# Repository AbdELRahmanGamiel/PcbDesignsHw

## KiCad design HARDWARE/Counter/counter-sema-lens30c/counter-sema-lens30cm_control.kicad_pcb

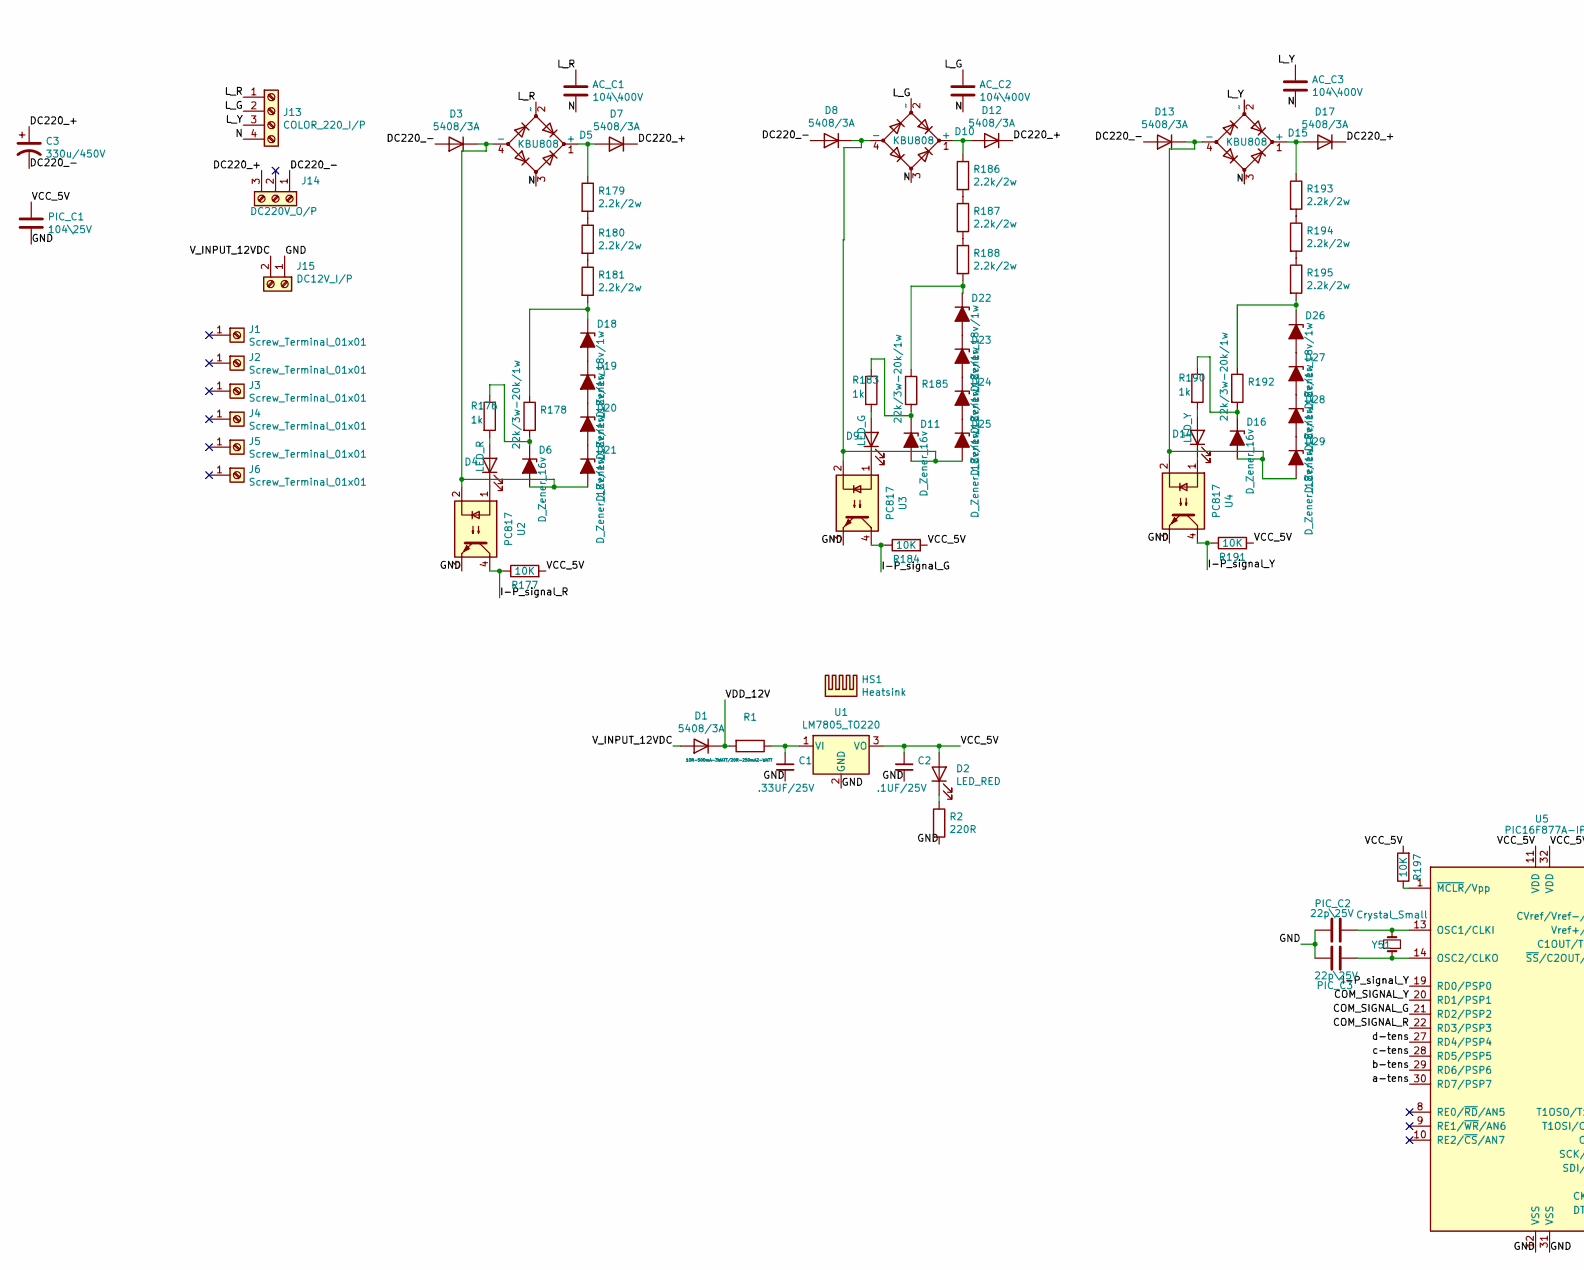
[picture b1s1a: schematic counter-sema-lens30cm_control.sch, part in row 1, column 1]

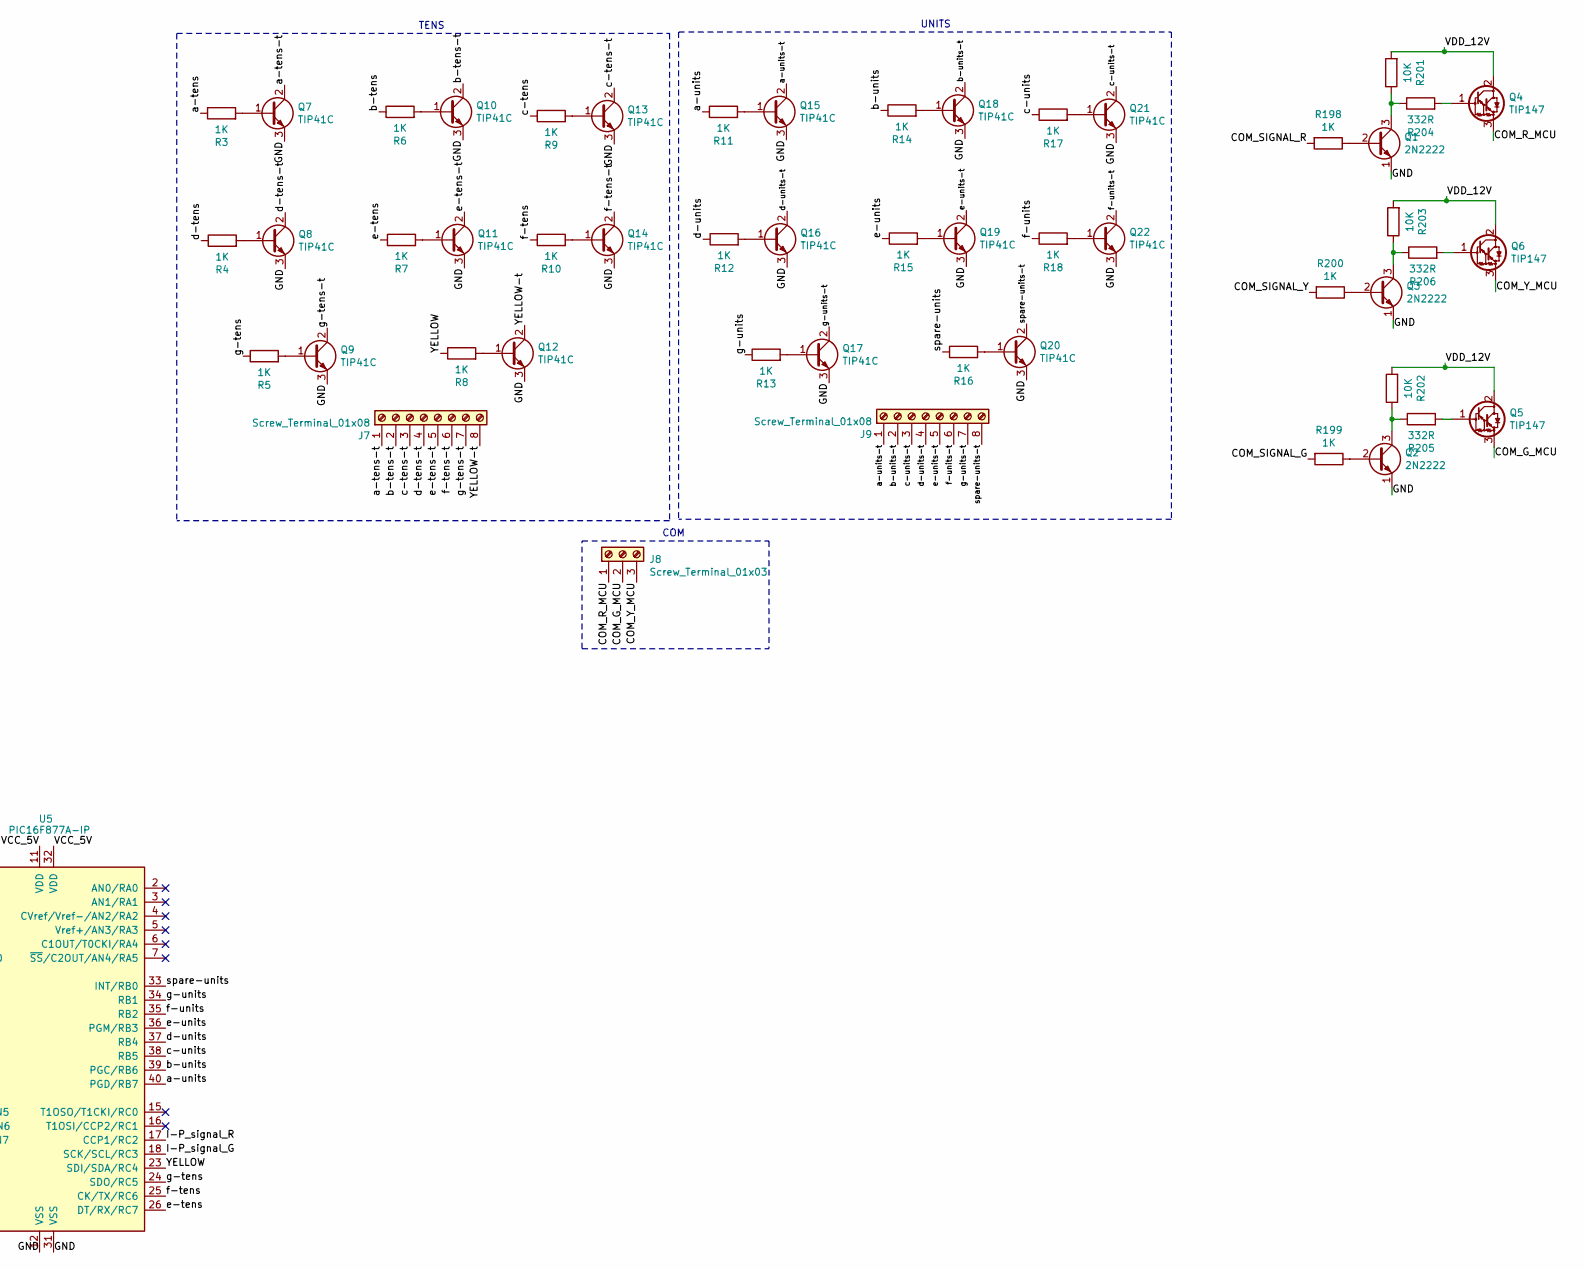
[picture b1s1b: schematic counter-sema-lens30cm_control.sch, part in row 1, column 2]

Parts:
AC_C1, AC_C2, AC_C3: 104\\400V; C_Rect_L13.0mm_W6.0mm_P10.00mm_FKS3_FKP3_MKS4
C1: .33UF/25V; C_Disc_D7.0mm_W2.5mm_P5.00mm
C2: .1UF/25V; C_Disc_D7.0mm_W2.5mm_P5.00mm
C3: 330u/450V; CP_Radial_D35.0mm_P10.00mm_SnapIn
D1, D3, D7, D8, D12, D13, D17: 5408/3A; D_DO-27_P15.24mm_Horizontal
D2: LED_RED; LED_D5.0mm
D4: LED_R; LED_D5.0mm
D5, D10, D15: KBU808; Diode_Bridge_Vishay_KBU
D6, D11, D16: D_Zener_16v; D_A-405_P7.62mm_Horizontal
D9: LED_G; LED_D5.0mm
D14: LED_Y; LED_D5.0mm
D18, D19, D20, D21, D22, D23, D24, D25, D26, D27, D28, D29: D_Zener_18v/1w; D_A-405_P7.62mm_Horizontal
HS1: Heatsink; Heatsink_Fischer_SK104-STC-STIC_35x13mm_2xDrill2.5mm
J1, J2, J3, J4, J5, J6: Screw_Terminal_01x01; TestPoint_Plated_Hole_D5.0mm
J7, J9: Screw_Terminal_01x08; PhoenixContact_MSTBA_2,5_8-G-5,08_1x08_P5.08mm_Horizontal
J8: Screw_Terminal_01x03; PhoenixContact_MSTBA_2,5_3-G-5,08_1x03_P5.08mm_Horizontal
J13: COLOR_220_I/P; PhoenixContact_MSTBA_2,5_4-G-5,08_1x04_P5.08mm_Horizontal
J14: DC220V_O/P; PhoenixContact_MSTBA_2,5_3-G-5,08_1x03_P5.08mm_Horizontal
J15: DC12V_I/P; PhoenixContact_MSTBA_2,5_2-G-5,08_1x02_P5.08mm_Horizontal
PIC_C1: 104\\25V; C_Disc_D7.0mm_W2.5mm_P5.00mm
PIC_C2, PIC_C3: 22p\\25V; C_Disc_D7.0mm_W2.5mm_P5.00mm
Q1, Q2, Q3: 2N2222; TO-92L_Wide
Q4, Q5, Q6: TIP147; TO-3P-3_Horizontal_TabDown
Q7, Q8, Q9, Q10, Q11, Q12, Q13, Q14, Q15, Q16, Q17, Q18, Q19, Q20, Q21, Q22: TIP41C; TO-220-3_Horizontal_TabDown
R1: 10R-500mA-3WATT/20R-250mA2-WATT; R_Axial_DIN0516_L15.5mm_D5.0mm_P20.32mm_Horizontal
R2: 220R; R_Axial_DIN0207_L6.3mm_D2.5mm_P10.16mm_Horizontal
R3, R4, R5, R6, R7, R8, R9, R10, R11, R12, R13, R14, R15, R16, R17, R18, R198, R199, R200: 1K; R_Axial_DIN0207_L6.3mm_D2.5mm_P10.16mm_Horizontal
R176, R183, R190: 1k; R_Axial_DIN0207_L6.3mm_D2.5mm_P10.16mm_Horizontal
R177, R184, R191, R197, R201, R202, R203: 10K; R_Axial_DIN0207_L6.3mm_D2.5mm_P10.16mm_Horizontal
R178, R185, R192: 22k/3w-20k/1w; R_Axial_Power_L25.0mm_W9.0mm_P30.48mm
R179, R180, R181, R186, R187, R188, R193, R194, R195: 2.2k/2w; R_Axial_DIN0516_L15.5mm_D5.0mm_P7.62mm_Vertical
R204, R205, R206: 332R; R_Axial_DIN0207_L6.3mm_D2.5mm_P10.16mm_Horizontal
U1: LM7805_TO220; TO-220-3_Vertical
U2, U3, U4: PC817; DIP-4_W7.62mm
U5: PIC16F877A-IP; DIP-40_W15.24mm_Socket_LongPads
Y51: Crystal_Small; Resonator-2Pin_W10.0mm_H5.0mm

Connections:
/COM_G_MCU: J8.2, Q5.3 (E)
/COM_R_MCU: J8.1, Q4.3 (E)
/COM_SIGNAL_G: R199.2, U5.21 (RD2/PSP2)
/COM_SIGNAL_R: R198.2, U5.22 (RD3/PSP3)
/COM_SIGNAL_Y: R200.2, U5.20 (RD1/PSP1)
/COM_Y_MCU: J8.3, Q6.3 (E)
/DC220_+: C3.1, D7.1 (K), D12.1 (K), D17.1 (K), J14.3
/DC220_-: C3.2, D3.2 (A), D8.2 (A), D13.2 (A), J14.1
/GND: C1.2, C2.2, J15.1, PIC_C1.2, PIC_C2.1, PIC_C3.1, Q1.1 (E), Q2.1 (E), Q3.1 (E), Q7.3 (E), Q8.3 (E), Q9.3 (E), Q10.3 (E), Q11.3 (E), Q12.3 (E), Q13.3 (E), Q14.3 (E), Q15.3 (E), Q16.3 (E), Q17.3 (E), Q18.3 (E), Q19.3 (E), Q20.3 (E), Q21.3 (E), Q22.3 (E), R2.2, U1.2 (GND), U2.3, U3.3, U4.3, U5.12 (VSS), U5.31 (VSS)
/I-P_signal_G: R184.1, U3.4, U5.18 (SCK/SCL/RC3)
/I-P_signal_R: R177.1, U2.4, U5.17 (CCP1/RC2)
/I-P_signal_Y: R191.1, U4.4, U5.19 (RD0/PSP0)
/L_G: AC_C2.1, D10.2 (~~), J13.2
/L_R: AC_C1.1, D5.2 (~~), J13.1
/L_Y: AC_C3.1, D15.2 (~~), J13.3
/N: AC_C1.2, AC_C2.2, AC_C3.2, D5.3 (~~), D10.3 (~~), D15.3 (~~), J13.4
/VCC_5V: C2.1, D2.2 (A), PIC_C1.1, R177.2, R184.2, R191.2, R197.2, U1.3 (VO), U5.11 (VDD), U5.32 (VDD)
/VDD_12V: D1.1 (K), Q4.2 (C), Q5.2 (C), Q6.2 (C), R1.2, R201.2, R202.2, R203.2
/V_INPUT_12VDC: D1.2 (A), J15.2
/YELLOW: R8.1, U5.23 (SDI/SDA/RC4)
/YELLOW-t: J7.8, Q12.2 (C)
/a-tens: R3.1, U5.30 (RD7/PSP7)
/a-tens-t: J7.1, Q7.2 (C)
/a-units: R11.1, U5.40 (PGD/RB7)
/a-units-t: J9.1, Q15.2 (C)
/b-tens: R6.1, U5.29 (RD6/PSP6)
/b-tens-t: J7.2, Q10.2 (C)
/b-units: R14.1, U5.39 (PGC/RB6)
/b-units-t: J9.2, Q18.2 (C)
/c-tens: R9.1, U5.28 (RD5/PSP5)
/c-tens-t: J7.3, Q13.2 (C)
/c-units: R17.1, U5.38 (RB5)
/c-units-t: J9.3, Q21.2 (C)
/d-tens: R4.1, U5.27 (RD4/PSP4)
/d-tens-t: J7.4, Q8.2 (C)
/d-units: R12.1, U5.37 (RB4)
/d-units-t: J9.4, Q16.2 (C)
/e-tens: R7.1, U5.26 (DT/RX/RC7)
/e-tens-t: J7.5, Q11.2 (C)
/e-units: R15.1, U5.36 (PGM/RB3)
/e-units-t: J9.5, Q19.2 (C)
/f-tens: R10.1, U5.25 (CK/TX/RC6)
/f-tens-t: J7.6, Q14.2 (C)
/f-units: R18.1, U5.35 (RB2)
/f-units-t: J9.6, Q22.2 (C)
/g-tens: R5.1, U5.24 (SDO/RC5)
/g-tens-t: J7.7, Q9.2 (C)
/g-units: R13.1, U5.34 (RB1)
/g-units-t: J9.7, Q17.2 (C)
/spare-units: R16.1, U5.33 (INT/RB0)
/spare-units-t: J9.8, Q20.2 (C)
unnamed: C1.1, R1.1, U1.1 (VI)
unnamed: D2.1 (K), R2.1
unnamed: D4.1 (K), U2.1
unnamed: D4.2 (A), R176.2
unnamed: D5.1 (+), D7.2 (A), R179.1
unnamed: D6.1 (K), R176.1, R178.2
unnamed: D9.1 (K), U3.1
unnamed: D9.2 (A), R183.2
unnamed: D10.1 (+), D12.2 (A), R186.1
unnamed: D8.1 (K), D10.4 (-), D11.2 (A), D25.2 (A), U3.2
unnamed: D11.1 (K), R183.1, R185.2
unnamed: D13.1 (K), D15.4 (-), D16.2 (A), D29.2 (A), U4.2
unnamed: D14.1 (K), U4.1
unnamed: D14.2 (A), R190.2
unnamed: D15.1 (+), D17.2 (A), R193.1
unnamed: D16.1 (K), R190.1, R192.2
unnamed: D18.1 (K), R178.1, R181.2
unnamed: D18.2 (A), D19.1 (K)
unnamed: D19.2 (A), D20.1 (K)
unnamed: D20.2 (A), D21.1 (K)
unnamed: D3.1 (K), D5.4 (-), D6.2 (A), D21.2 (A), U2.2
unnamed: D22.1 (K), R185.1, R188.2
unnamed: D22.2 (A), D23.1 (K)
unnamed: D23.2 (A), D24.1 (K)
unnamed: D24.2 (A), D25.1 (K)
unnamed: D26.1 (K), R192.1, R195.2
unnamed: D26.2 (A), D27.1 (K)
unnamed: D27.2 (A), D28.1 (K)
unnamed: D28.2 (A), D29.1 (K)
unnamed: PIC_C2.2, U5.13 (OSC1/CLKI), Y51.2
unnamed: PIC_C3.2, U5.14 (OSC2/CLKO), Y51.1
unnamed: Q1.2 (B), R198.1
unnamed: Q1.3 (C), R201.1, R204.1
unnamed: Q2.2 (B), R199.1
unnamed: Q2.3 (C), R202.1, R205.1
unnamed: Q3.2 (B), R200.1
unnamed: Q3.3 (C), R203.1, R206.1
unnamed: Q4.1 (B), R204.2
unnamed: Q5.1 (B), R205.2
unnamed: Q6.1 (B), R206.2
unnamed: Q7.1 (B), R3.2
unnamed: Q8.1 (B), R4.2
unnamed: Q9.1 (B), R5.2
unnamed: Q10.1 (B), R6.2
unnamed: Q11.1 (B), R7.2
unnamed: Q12.1 (B), R8.2
unnamed: Q13.1 (B), R9.2
unnamed: Q14.1 (B), R10.2
unnamed: Q15.1 (B), R11.2
unnamed: Q16.1 (B), R12.2
unnamed: Q17.1 (B), R13.2
unnamed: Q18.1 (B), R14.2
unnamed: Q19.1 (B), R15.2
unnamed: Q20.1 (B), R16.2
unnamed: Q21.1 (B), R17.2
unnamed: Q22.1 (B), R18.2
unnamed: R179.2, R180.1
unnamed: R180.2, R181.1
unnamed: R186.2, R187.1
unnamed: R187.2, R188.1
unnamed: R193.2, R194.1
unnamed: R194.2, R195.1
unnamed: R197.1, U5.1 (~MCLR~/Vpp)

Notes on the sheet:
UNITS
TENS
COM

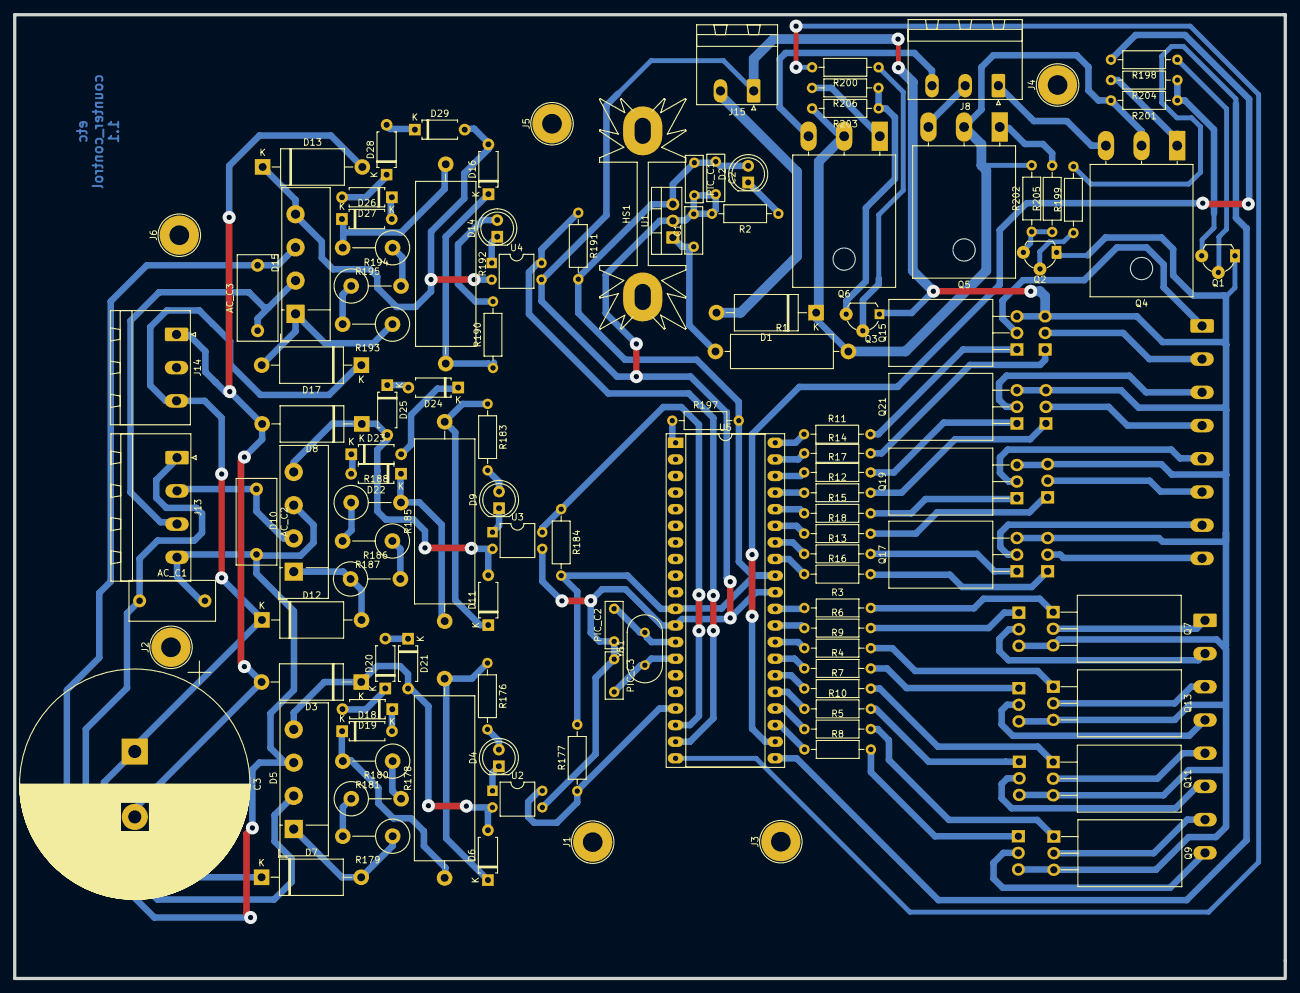
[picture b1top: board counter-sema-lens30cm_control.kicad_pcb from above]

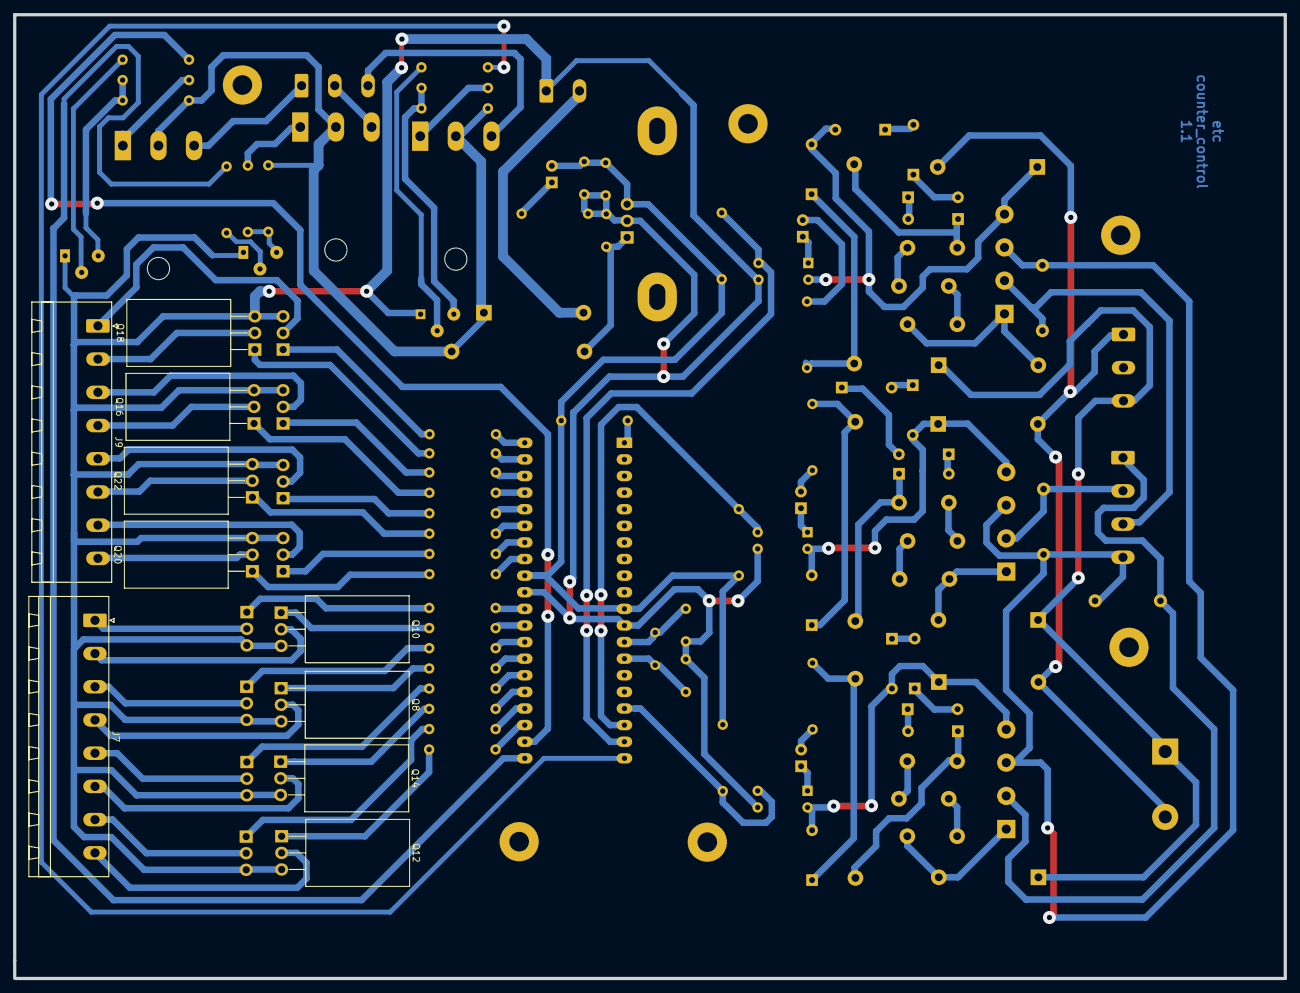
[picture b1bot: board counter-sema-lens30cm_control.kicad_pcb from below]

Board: 2 copper layers, 194.3 x 147.4 mm, 125 parts (10 on the bottom side), 114 nets.

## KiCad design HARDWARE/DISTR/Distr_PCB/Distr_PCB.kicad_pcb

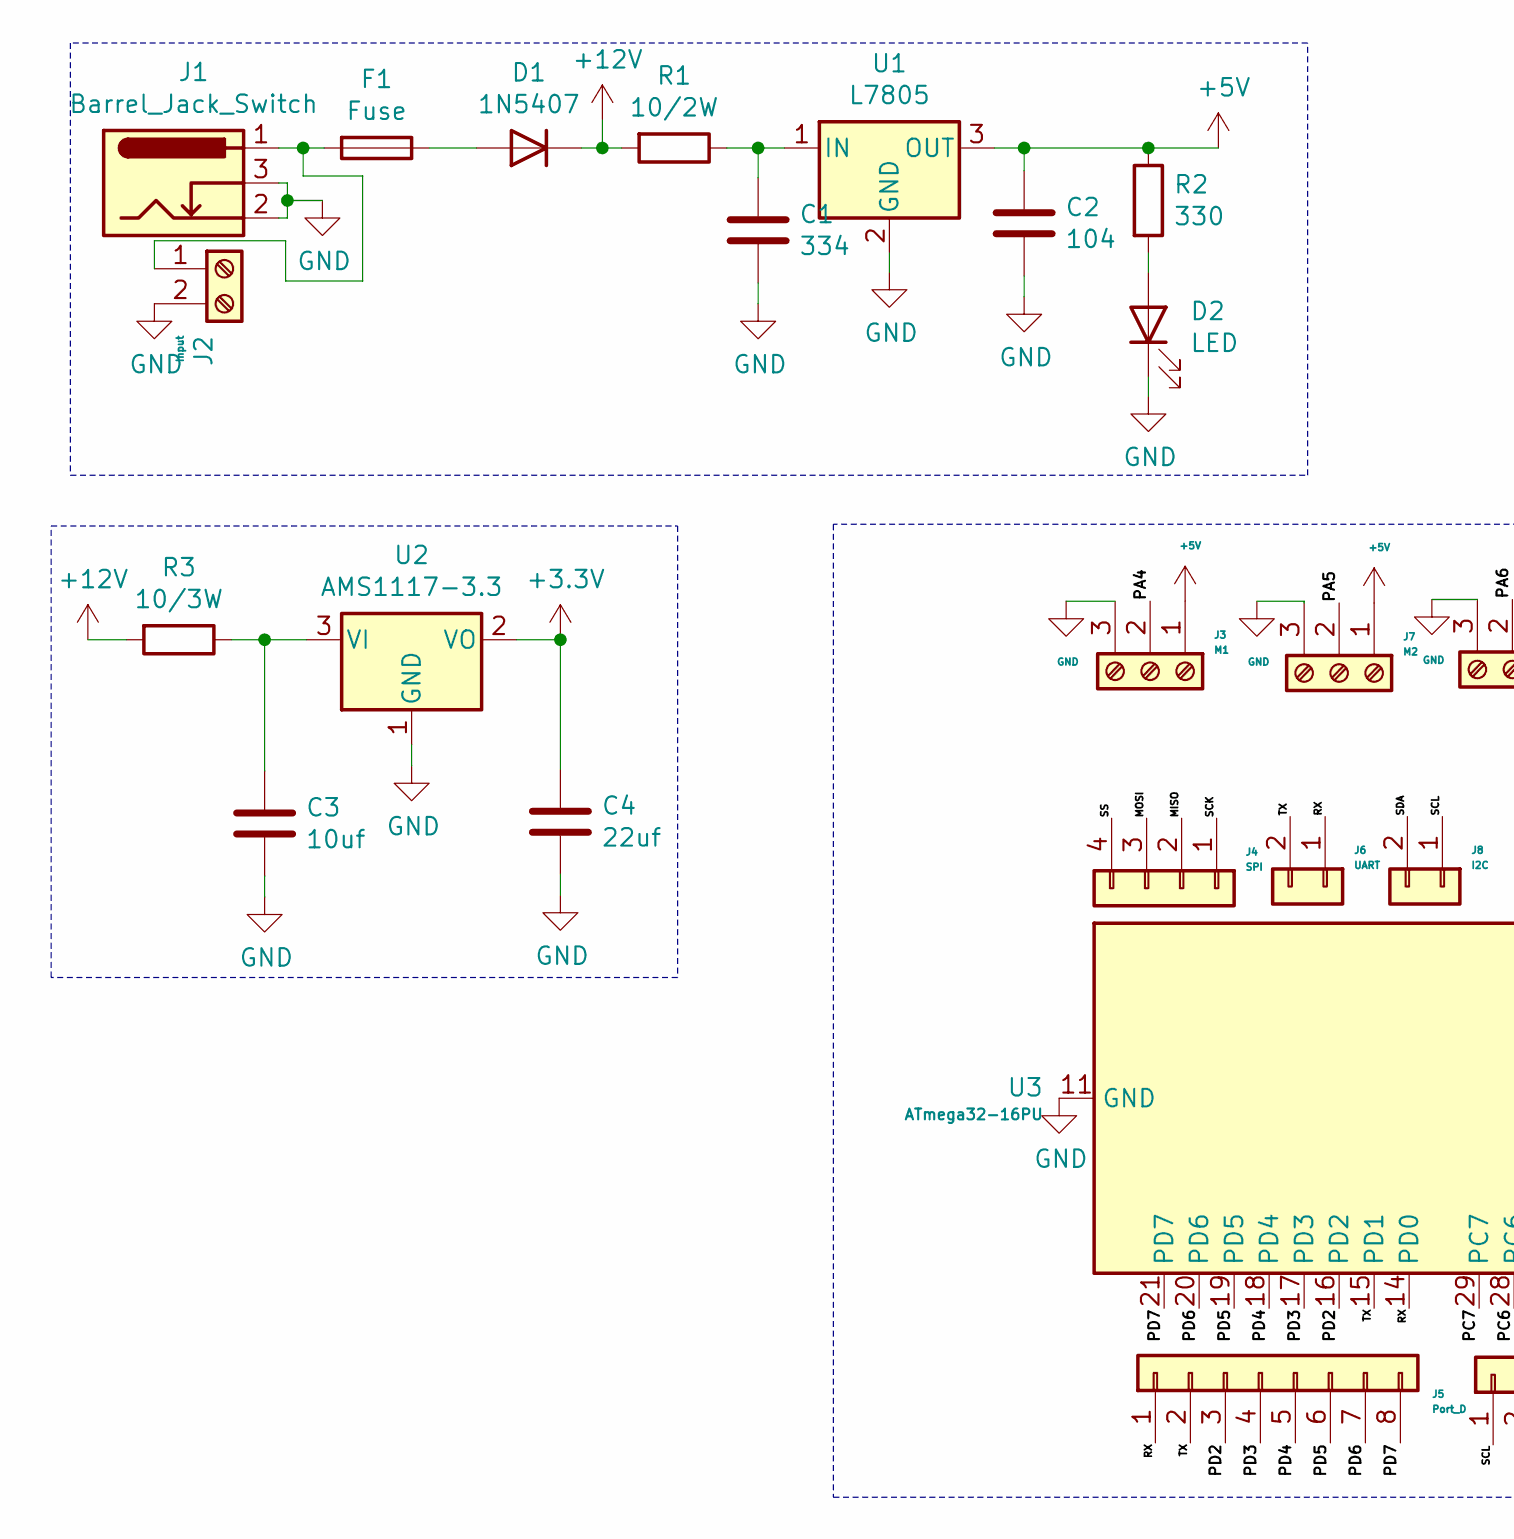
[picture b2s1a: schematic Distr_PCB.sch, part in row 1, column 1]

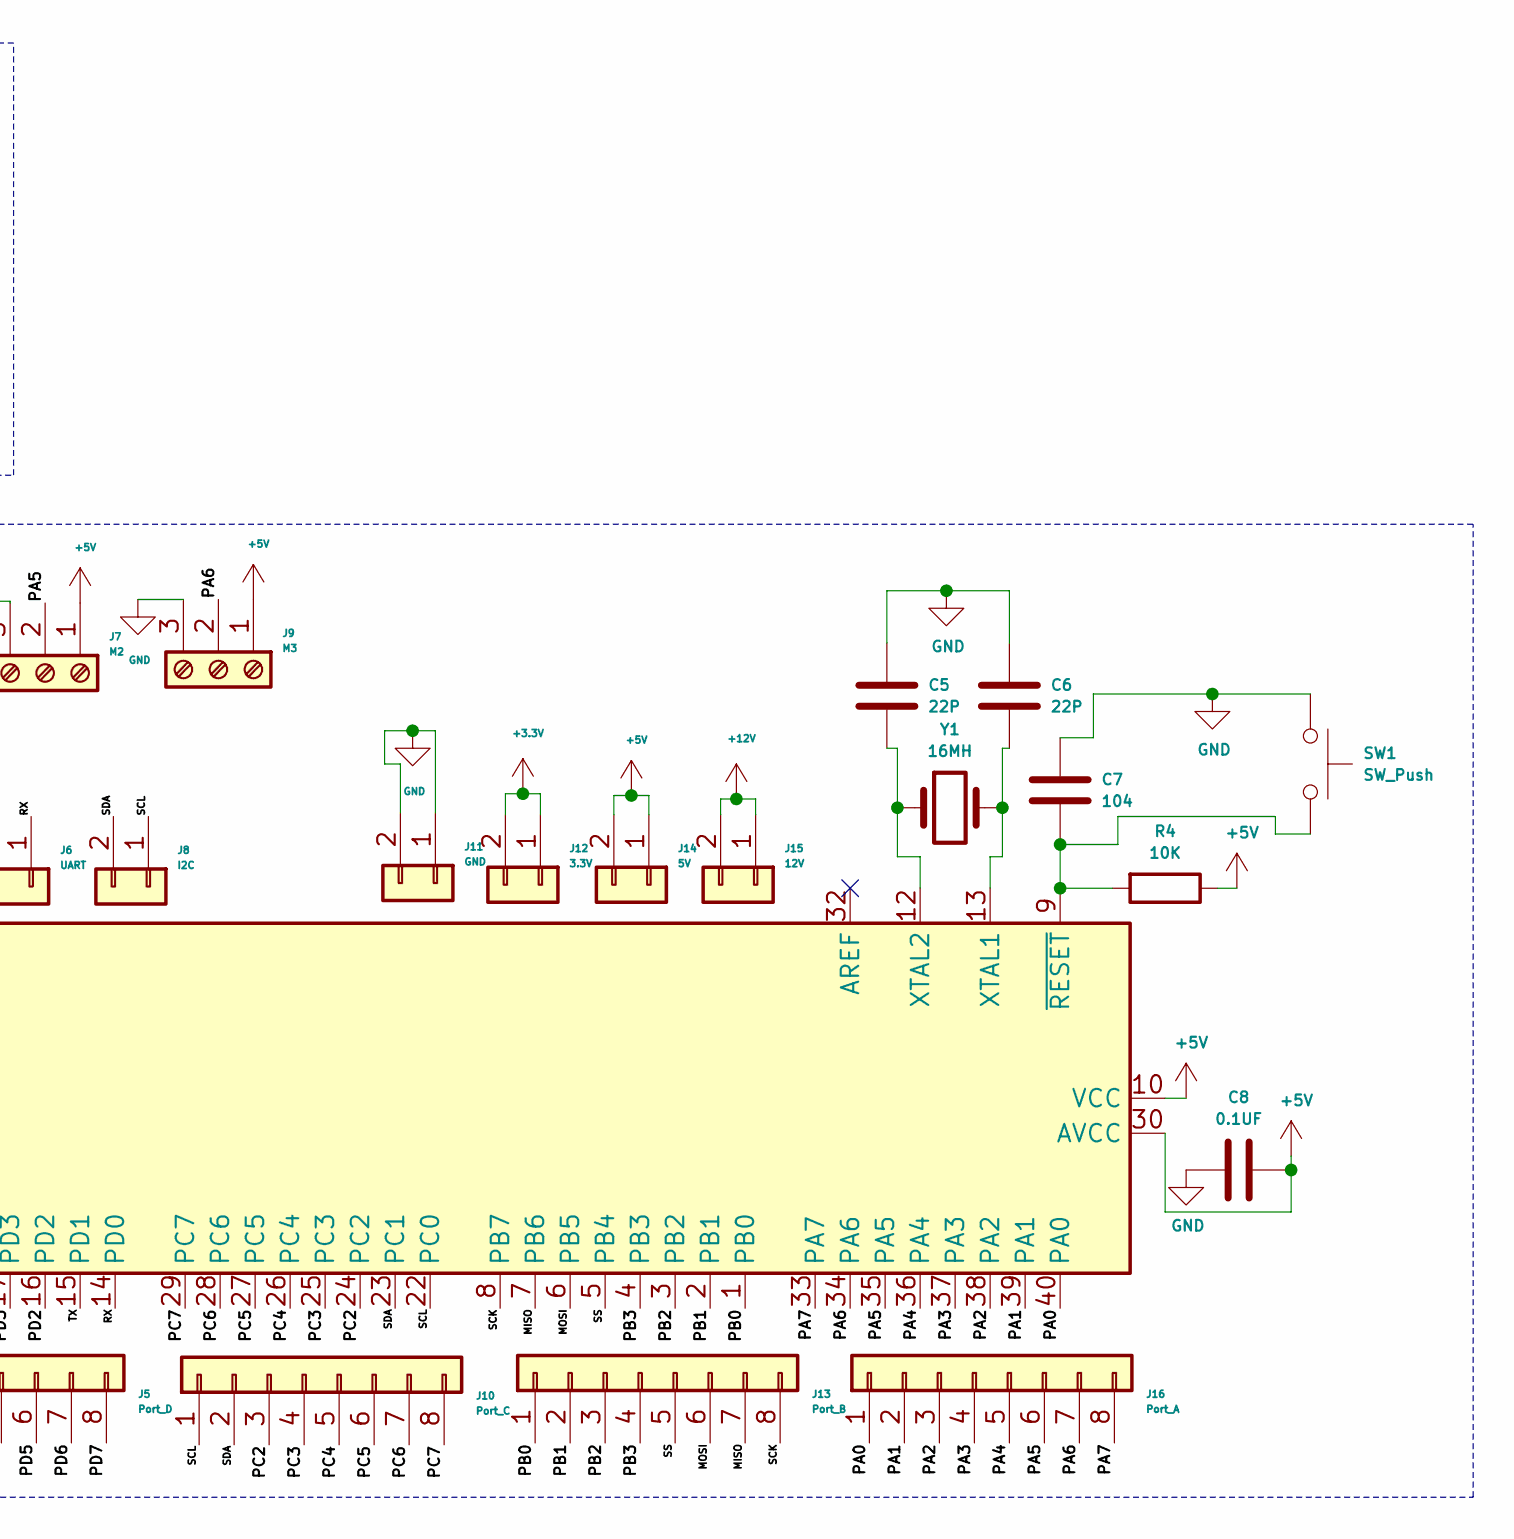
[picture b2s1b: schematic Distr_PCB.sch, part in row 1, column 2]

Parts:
C1: 334; C_Disc_D7.0mm_W2.5mm_P5.00mm
C2, C7: 104; C_Disc_D7.0mm_W2.5mm_P5.00mm
C3: 10uf; C_Disc_D7.0mm_W2.5mm_P5.00mm
C4: 22uf; C_Disc_D7.0mm_W2.5mm_P5.00mm
C5, C6: 22P; C_Disc_D7.0mm_W2.5mm_P5.00mm
C8: 0.1UF; C_Disc_D7.0mm_W2.5mm_P5.00mm
D1: 1N5407; D_DO-201AD_P15.24mm_Horizontal
D2: LED; LED_D5.0mm
F1: Fuse; Fuseholder_Cylinder-5x20mm_Schurter_0031_8201_Horizontal_Op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
J1: Barrel_Jack_Switch; BarrelJack_Horizontal
J2: Input; Altech_AK300_1x02_P5.00mm_45-Degree
J3: M1; Altech_AK300_1x03_P5.00mm_45-Degree
J4: SPI; PinHeader_1x04_P2.54mm_Vertical
J5: Port_D; PinHeader_1x08_P2.54mm_Vertical
J6: UART; PinHeader_1x02_P2.54mm_Vertical
J7: M2; Altech_AK300_1x03_P5.00mm_45-Degree
J8: I2C; PinHeader_1x02_P2.54mm_Vertical
J9: M3; Altech_AK300_1x03_P5.00mm_45-Degree
J10: Port_C; PinHeader_1x08_P2.54mm_Vertical
J11: GND; PinHeader_1x02_P2.54mm_Vertical
J12: 3.3V; PinHeader_1x02_P2.54mm_Vertical
J13: Port_B; PinHeader_1x08_P2.54mm_Vertical
J14: 5V; PinHeader_1x02_P2.54mm_Vertical
J15: 12V; PinHeader_1x02_P2.54mm_Vertical
J16: Port_A; PinHeader_1x08_P2.54mm_Vertical
R1: 10/2W; R_Axial_Power_L20.0mm_W6.4mm_P25.40mm
R2: 330; R_Axial_DIN0207_L6.3mm_D2.5mm_P10.16mm_Horizontal
R3: 10/3W; R_Axial_Power_L20.0mm_W6.4mm_P25.40mm
R4: 10K; R_Axial_DIN0207_L6.3mm_D2.5mm_P10.16mm_Horizontal
SW1: SW_Push; SW_PUSH_6mm_H7.3mm
U1: L7805; TO-220-3_Vertical
U2: AMS1117-3.3; SOT-223-3_TabPin2
U3: ATmega32-16PU; DIP-40_W15.24mm
Y1: 16MH; Resonator-2Pin_W10.0mm_H5.0mm

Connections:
+3V3: C4.1, J12.1, J12.2, U2.2 (VO)
+5V: C2.1, C8.1, J3.1, J7.1, J9.1, J14.1, J14.2, R2.1, R4.1, U1.3 (OUT), U3.10 (VCC), U3.30 (AVCC)
+12V: D1.1 (K), J15.1, J15.2, R1.2, R3.2
/MISO: J4.2, J13.7, U3.7 (PB6)
/MOSI: J4.3, J13.6, U3.6 (PB5)
/PA0: J16.1, U3.40 (PA0)
/PA1: J16.2, U3.39 (PA1)
/PA2: J16.3, U3.38 (PA2)
/PA3: J16.4, U3.37 (PA3)
/PA4: J3.2, J16.5, U3.36 (PA4)
/PA5: J7.2, J16.6, U3.35 (PA5)
/PA6: J9.2, J16.7, U3.34 (PA6)
/PA7: J16.8, U3.33 (PA7)
/PB0: J13.1, U3.1 (PB0)
/PB1: J13.2, U3.2 (PB1)
/PB2: J13.3, U3.3 (PB2)
/PB3: J13.4, U3.4 (PB3)
/PC2: J10.3, U3.24 (PC2)
/PC3: J10.4, U3.25 (PC3)
/PC4: J10.5, U3.26 (PC4)
/PC5: J10.6, U3.27 (PC5)
/PC6: J10.7, U3.28 (PC6)
/PC7: J10.8, U3.29 (PC7)
/PD2: J5.3, U3.16 (PD2)
/PD3: J5.4, U3.17 (PD3)
/PD4: J5.5, U3.18 (PD4)
/PD5: J5.6, U3.19 (PD5)
/PD6: J5.7, U3.20 (PD6)
/PD7: J5.8, U3.21 (PD7)
/RX: J5.1, J6.1, U3.14 (PD0)
/SCK: J4.1, J13.8, U3.8 (PB7)
/SCL: J8.1, J10.1, U3.22 (PC0)
/SDA: J8.2, J10.2, U3.23 (PC1)
/SS: J4.4, J13.5, U3.5 (PB4)
/TX: J5.2, J6.2, U3.15 (PD1)
GND: C1.2, C2.2, C3.2, C4.2, C5.2, C6.2, C7.2, C8.2, D2.1 (K), J1.2, J1.3, J2.2, J3.3, J7.3, J9.3, J11.1, J11.2, SW1.1, U1.2 (GND), U2.1 (GND), U3.11 (GND), U3.31 (GND)
unnamed: C1.1, R1.1, U1.1 (IN)
unnamed: C3.1, R3.1, U2.3 (VI)
unnamed: C5.1, U3.12 (XTAL2), Y1.1
unnamed: C6.1, U3.13 (XTAL1), Y1.2
unnamed: C7.1, R4.2, SW1.2, U3.9 (~RESET)
unnamed: D1.2 (A), F1.1
unnamed: D2.2 (A), R2.2
unnamed: F1.2, J1.1, J2.1

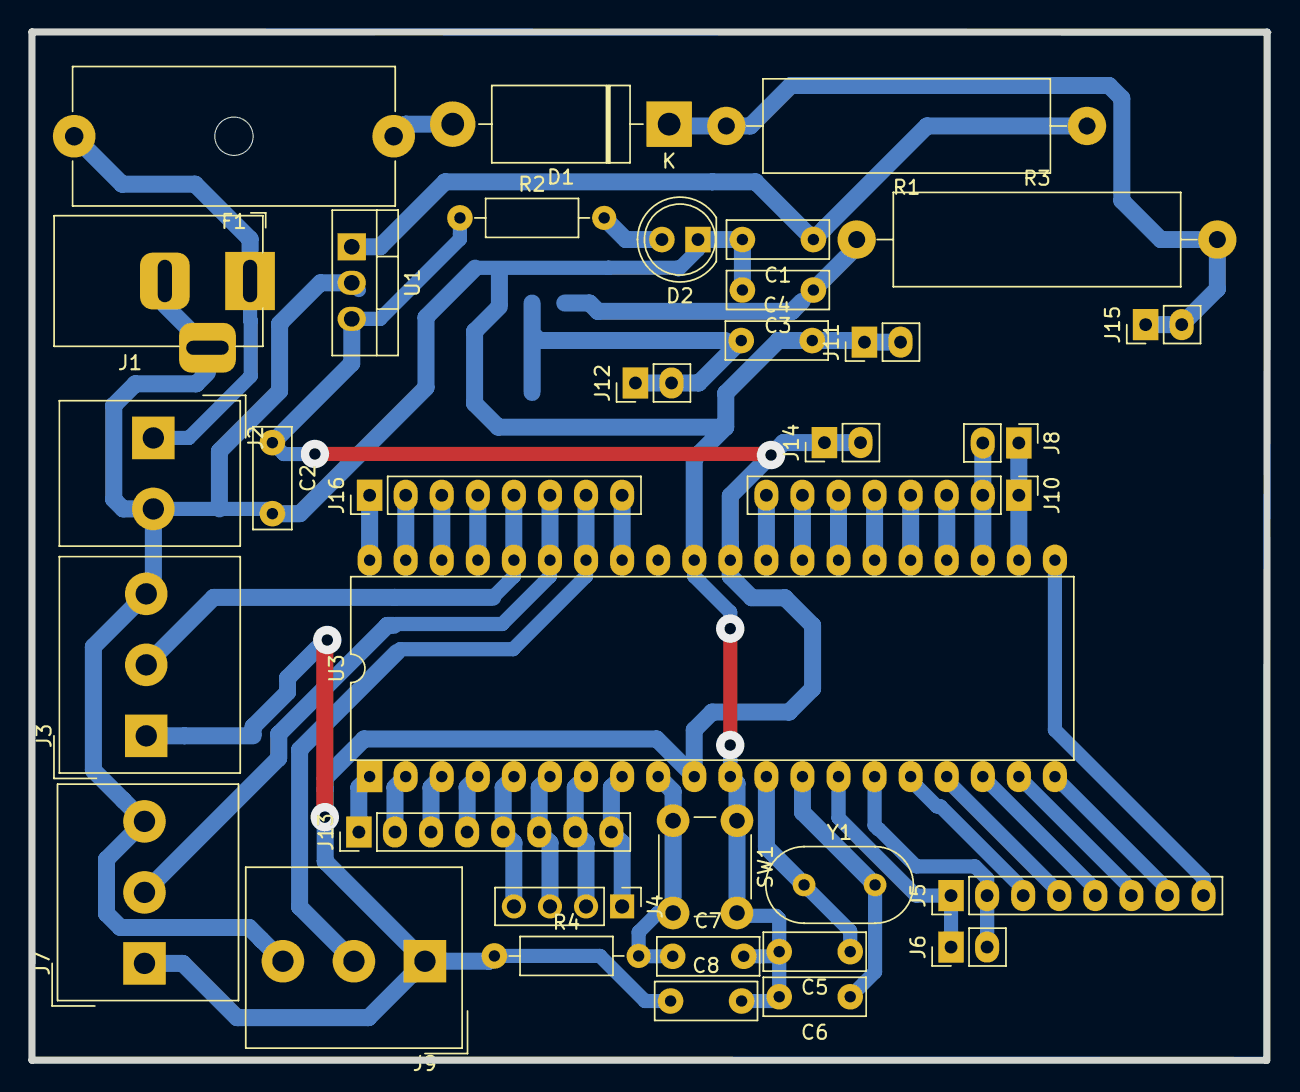
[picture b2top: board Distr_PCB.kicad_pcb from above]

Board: 2 copper layers, 87.0 x 72.4 mm, 36 parts (1 on the bottom side), 44 nets.

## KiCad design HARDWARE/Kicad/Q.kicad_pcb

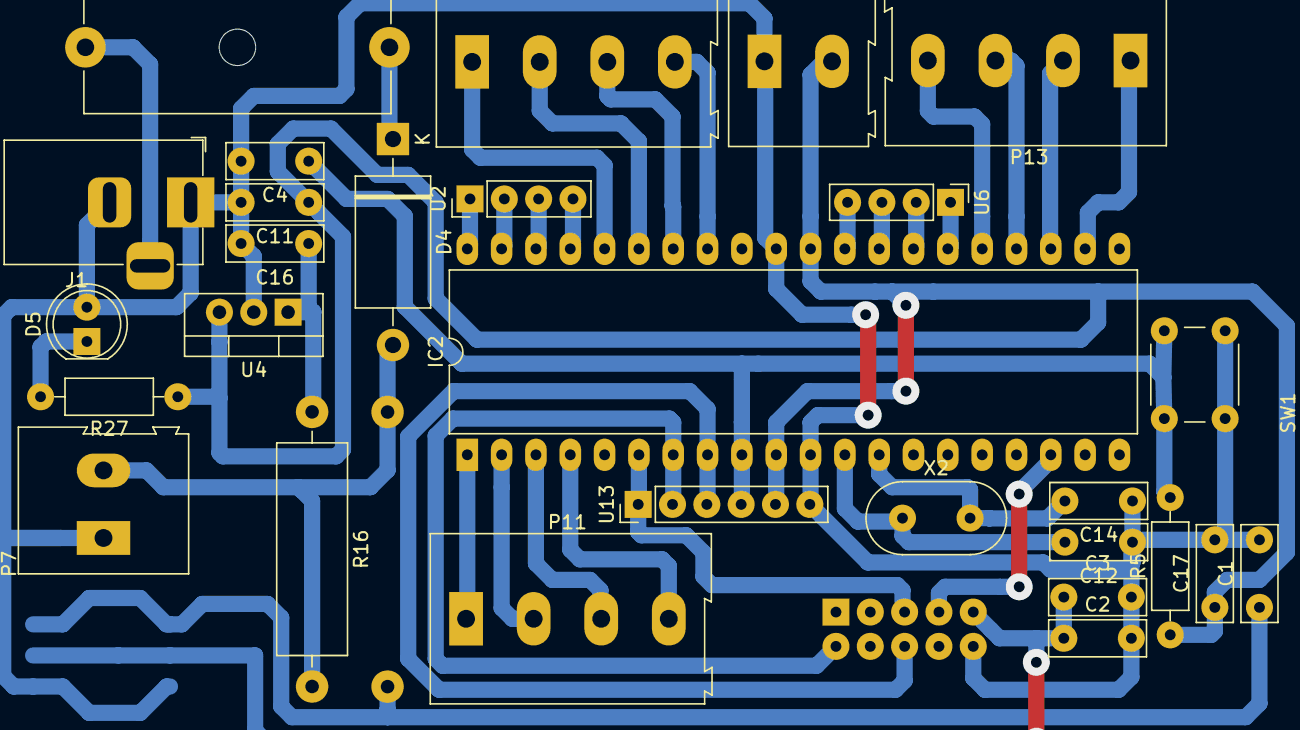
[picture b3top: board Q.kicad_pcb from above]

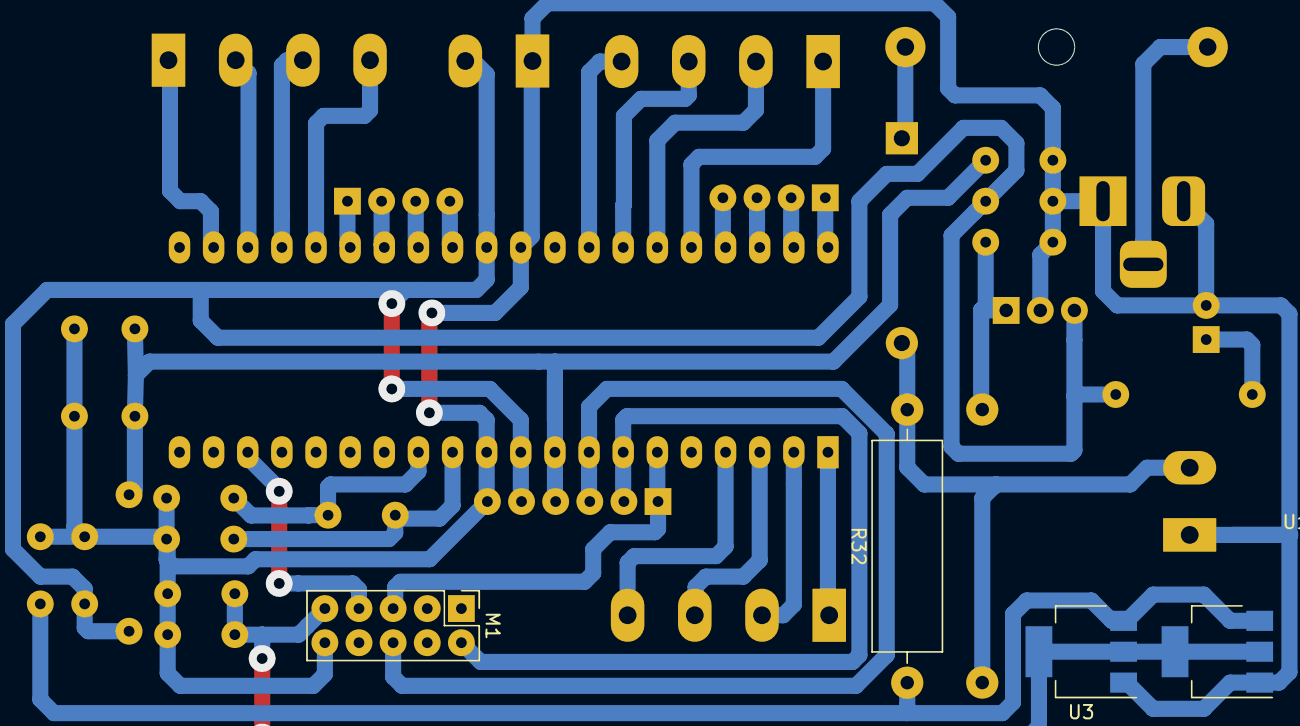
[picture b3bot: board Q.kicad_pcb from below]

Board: 2 copper layers, 32 parts (4 on the bottom side), 36 nets.

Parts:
C1, C2, C3: CP1; C_Disc_D7.0mm_W2.5mm_P5.00mm
C4, C17: 104; C_Disc_D7.0mm_W2.5mm_P5.00mm
C11: 0.1UF; C_Disc_D7.0mm_W2.5mm_P5.00mm
C12, C14: 22P; C_Disc_D7.0mm_W2.5mm_P5.00mm
C16: 334; C_Disc_D7.0mm_W2.5mm_P5.00mm
D4: DIODE 3A; D_DO-27_P15.24mm_Horizontal
D5: LED; LED_D5.0mm
F2: FUSE; Fuseholder_Cylinder-5x20mm_Schurter_0031_8201_Horizontal_Op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
IC2: ATMEGA32-P; DIP-40_W15.24mm_LongPads
J1: JACK_2P; BarrelJack_Horizontal
M1: Ethernet_module; PinHeader_2x05_P2.54mm_Vertical
P7: power to micro; TerminalBlock_Altech_AK300-2_P5.00mm
P9: Digit2; TerminalBlock_Altech_AK300-4_P5.00mm
P10: power to7447; TerminalBlock_Altech_AK300-2_P5.00mm
P11: Digit1; TerminalBlock_Altech_AK300-4_P5.00mm
P13: Digit3; TerminalBlock_Altech_AK300-4_P5.00mm
R5: 10k; R_Axial_DIN0207_L6.3mm_D2.5mm_P10.16mm_Horizontal
R16: R 2W; R_Axial_DIN0516_L15.5mm_D5.0mm_P20.32mm_Horizontal
R27: 330R; R_Axial_DIN0207_L6.3mm_D2.5mm_P10.16mm_Horizontal
R32: 10K/3W; R_Axial_DIN0516_L15.5mm_D5.0mm_P20.32mm_Horizontal
SW1: SW_PUSH; SW_PUSH_6mm_H7.3mm
U1, U3: AMS1117-3.3; SOT-223-3_TabPin2
U2, U6: 4PIN; PinHeader_1x04_P2.54mm_Vertical
U4: L7805; TO-220-3_Vertical
U13: Spi; PinHeader_1x06_P2.54mm_Vertical
X2: XTAL; Resonator-2Pin_W10.0mm_H5.0mm

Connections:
+3.3V: C2.1, C3.1, M1.9, U1.2, U3.2
+12V: D4.2, P7.2, R16.2, R32.2
/CS(PD4): IC2.18, M1.7
/RESET: C4.1, IC2.9, R5.2, SW1.2, U13.4
/sck: IC2.8, M1.6, U13.3
/si: IC2.6, M1.5, U13.1
/so: IC2.7, M1.2, U13.2
GND: C1.2, C2.2, C3.2, C4.2, C11.2, C12.1, C14.1, C16.2, C17.2, D5.2, IC2.11, IC2.31, J1.1, J1.2, M1.10, P7.1, P10.1, SW1.1, U1.1, U3.1, U4.2, U13.6
unnamed: C1.1, R32.1, U1.3, U3.3
unnamed: C12.2, IC2.12, X2.1
unnamed: C14.2, IC2.13, X2.2
unnamed: C16.1, R16.1, U4.1
unnamed: D4.1, F2.2
unnamed: D5.1, R27.2
unnamed: F2.1, J1.3
unnamed: IC2.1, P11.1
unnamed: IC2.2, P11.2
unnamed: IC2.3, P11.3
unnamed: IC2.4, P11.4
unnamed: IC2.22, P13.1
unnamed: IC2.23, P13.2
unnamed: IC2.24, P13.3
unnamed: IC2.25, P13.4
unnamed: IC2.26, U6.1
unnamed: IC2.27, U6.2
unnamed: IC2.28, U6.3
unnamed: IC2.29, U6.4
unnamed: IC2.33, P9.4
unnamed: IC2.34, P9.3
unnamed: IC2.35, P9.2
unnamed: IC2.36, P9.1
unnamed: IC2.37, U2.4
unnamed: IC2.38, U2.3
unnamed: IC2.39, U2.2
unnamed: IC2.40, U2.1
VCC: C11.1, C17.1, IC2.10, IC2.30, P10.2, R5.1, R27.1, U4.3, U13.5
